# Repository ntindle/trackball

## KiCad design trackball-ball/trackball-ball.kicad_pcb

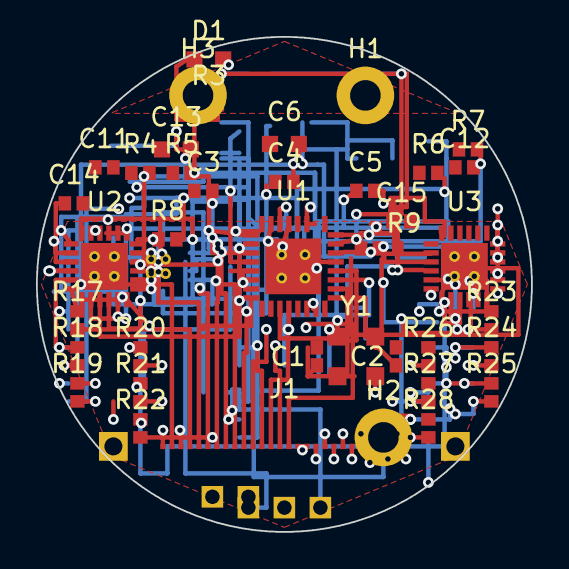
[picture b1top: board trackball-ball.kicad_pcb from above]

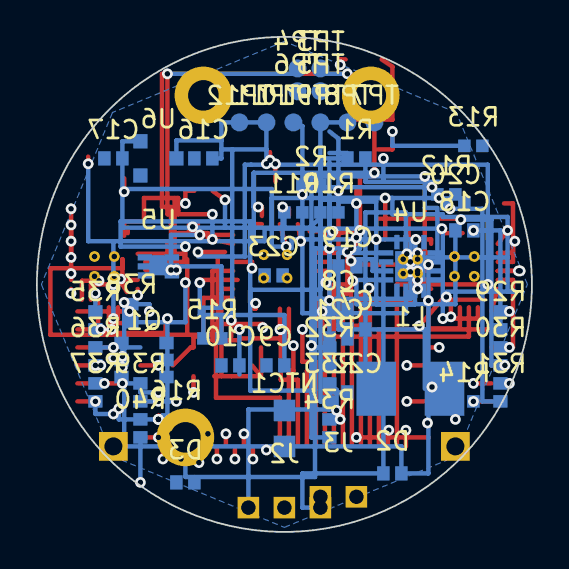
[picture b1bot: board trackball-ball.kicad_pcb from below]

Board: 4 copper layers, 27.5 x 27.5 mm, 92 parts (53 on the bottom side), 85 nets.

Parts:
C1, C2: 12pF-NP0; C_0402_1005Metric
C3, C4, C5, C11, C12: 100nF-X7R-0402; C_0402_1005Metric
C6, C13: 4.7uF-X7R-0603-10V; C_0603_1608Metric
C7, C8, C9, C10: 100nF-X7R-0402-10V; C_0402_1005Metric
C14, C15: 2.2nF-NP0-0402; C_0402_1005Metric
C16, C17: 1uF-X7R-0603-10V; C_0402_1005Metric
C18: 2.2uF-X7R-0603-10V; C_0402_1005Metric
C19, C23: 0.1uF-0603-10V; C_0402_1005Metric
C20: 10uF-X7R-0603-10V; C_0402_1005Metric
C21: 22uF-X5R-0603-10V; C_0402_1005Metric
C22: DHC-TBD-0603; C_0402_1005Metric
D1: GREEN-0603; LED-0603_1608Metric
D2, D3: TPD1E05U06; ESD-1005-2P
H1, H2, H3: M1.6-NPTH; MOUNT-HOLE-3.2
J1: FH28D-28S; FH28D-28S-0.5SH
J2: JST-PH-3; JST-PH-3_SMD-TH
J3: JST-PH-2; JST-PH-2_SMD-TH
L1: 47uH-SLF6028; IND-SLF6028-6x6
NTC1: 10k-NTC-flying; NTC-PADS-2P
Q1: DMG6968U; SOT-23-6_2.9x1.6mm
R1: 1M-1pct-0402; R_0402_1005Metric
R2: 330k-1pct-0402; R_0402_1005Metric
R3: 200R-0402; R_0402_1005Metric
R4, R5: 4.7k-0402; R_0402_1005Metric
R6, R7, R8, R9: 10k-0402; R_0402_1005Metric
R10, R11: 10k; R_0402_1005Metric
R12: 150k; R_0402_1005Metric
R13: 100k; R_0402_1005Metric
R14: 20k-1pct; R_0402_1005Metric
R15: 1M-1pct; R_0402_1005Metric
R16: 330k-1pct; R_0402_1005Metric
R17, R18, R19, R20, R21, R22, R23, R24, R25, R26, R27, R28, R29, R30, R31, R32, R33, R34, R35, R36, R37, R38, R39, R40: 560R-0402; R_0402_1005Metric
TP3: SWDIO; TP-PAD-D1.0
TP4: SWDCLK; TP-PAD-D1.0
TP5: +3V0; TP-PAD-D1.0
TP6: GND; TP-PAD-D1.0
TP7: NRESET_TP; TP-PAD-D1.0
TP8: TP_SPARE; TP-PAD-D1.0
TP9: CHRG; TP-PAD-D1.0
TP10: FAULT; TP-PAD-D1.0
TP11: VBAT; TP-PAD-D1.0
TP12: CELL_N; TP-PAD-D1.0
U1: NRF52810-QCAA; QFN-32-1EP_5x5mm_P0.5mm
U2: CY8CMBR3116-0x37; QFN-24-1EP_4x4mm_P0.5mm
U3: CY8CMBR3116-0x38; QFN-24-1EP_4x4mm_P0.5mm
U4: LTC4120-4.2; QFN-16-1EP_3x3mm_P0.5mm
U5: BQ29700; WSON-6-EP_2x2mm_P0.65mm
U6: XC6206P302; SOT-23_2.9x1.3mm
Y1: 32MHz-CL9pF; Crystal-3225-4P

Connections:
+3V0: C3.1, C4.1, C5.1, C6.1, C11.1, C12.1, C13.1, C17.1, R4.1, R5.1, R6.1, R7.1, R8.1, R9.1, R10.2, R11.2, TP5.1, U1.9, U1.25, U1.32, U2.7, U3.7, U6.2
ANT_FEED: J1.2, U1.19
CELL_N: C23.2, J3.2, Q1.6, TP12.1, U5.4, U5.7
CHRG: R10.1, TP9.1, U1.6, U4.14
DHC_SNS: C22.2, J2.3
DHC_U4: C22.1, U4.6
FAULT: R11.1, TP10.1, U1.5, U4.15
GND: C1.2, C2.2, C3.2, C4.2, C5.2, C6.2, C7.2, C8.2, C9.2, C10.2, C11.2, C12.2, C13.2, C14.2, C15.2, C16.2, C17.2, C18.1, C20.2, C21.2, D1.2, D2.2, D3.2, J1.1, J1.3, J1.16, J2.2, NTC1.2, Q1.4, R2.2, R13.2, R14.2, R16.2, TP6.1, U1.20, U1.29, U1.33, U2.6, U2.8, U2.9, U2.10, U2.11, U2.12, U2.25, U3.6, U3.8, U3.9, U3.10, U3.11, U3.12, U3.25, U4.5, U4.7, U4.17, U6.1, Y1.2, Y1.4
HI1: R6.2, U1.10, U2.23
HI2: R7.2, U1.11, U3.23
I2C_SCL: D3.1, R5.2, U1.8, U2.22, U3.22
I2C_SDA: D2.1, R4.2, U1.7, U2.21, U3.21
LED_A: D1.1, R3.2
LED_DOT: R3.1, U1.14
NTC_CELL: NTC1.1, U4.12
RUN_RX: R12.2, R13.1, U4.16
SW_RX: C19.2, L1.1, U4.4
T00: J1.4, R17.2
T01: J1.5, R18.2
T02: J1.6, R19.2
T03: J1.7, R20.2
T04: J1.8, R21.2
T05: J1.9, R22.2
T06: J1.10, R23.2
T07: J1.11, R24.2
T08: J1.12, R25.2
T09: J1.13, R26.2
T10: J1.14, R27.2
T11: J1.15, R28.2
T12: J1.17, R29.2
T13: J1.18, R30.2
T14: J1.19, R31.2
T15: J1.20, R32.2
T16: J1.21, R33.2
T17: J1.22, R34.2
T18: J1.23, R35.2
T19: J1.24, R36.2
T20: J1.25, R37.2
T21: J1.26, R38.2
T22: J1.27, R39.2
T23: J1.28, R40.2
U1_DEC3: C9.1, U1.22
U1_DEC4: C10.1, U1.30
U2_CMOD: C14.1, U2.5
U2_CS0: R17.1, U2.1
U2_CS1: R18.1, U2.2
U2_CS2: R19.1, U2.3
U2_CS3: R20.1, U2.4
U2_CS4: R21.1, U2.20
U2_CS5: R22.1, U2.19
U2_CS6: R23.1, U2.18
U2_CS7: R24.1, U2.17
U2_CS8: R25.1, U2.16
U2_CS9: R26.1, U2.15
U2_CS10: R27.1, U2.14
U2_CS11: R28.1, U2.13
U3_CMOD: C15.1, U3.5
U3_CS0: R29.1, U3.1
U3_CS1: R30.1, U3.2
U3_CS2: R31.1, U3.3
U3_CS3: R32.1, U3.4
U3_CS4: R33.1, U3.20
U3_CS5: R34.1, U3.19
U3_CS6: R35.1, U3.18
U3_CS7: R36.1, U3.17
U3_CS8: R37.1, U3.16
U3_CS9: R38.1, U3.15
U3_CS10: R39.1, U3.14
U3_CS11: R40.1, U3.13
U4_BOOST: C19.1, U4.2
U4_CHGSNS: L1.2, U4.8
U4_INTVCC: C18.2, U4.1
U4_PROG: R14.1, U4.13
U5_BAT: C23.1, R15.2, U5.5
U5_COUT: Q1.5, U5.2
U5_DOUT: Q1.2, U5.3
U5_MID: Q1.1, Q1.3
U5_VM: R16.1, U5.6
VBAT: C16.1, C21.1, J3.1, R1.1, R15.1, TP11.1, U4.9, U4.10, U6.3
VBAT_SNS: R1.2, R2.1, U1.4
VIN_RX: C20.1, J2.1, R12.1, U4.3
XC_A: C1.1, U1.23, Y1.1
XC_B: C2.1, U1.24, Y1.3
XRES1: R8.2, U1.12, U2.24
XRES2: R9.2, U1.13, U3.24

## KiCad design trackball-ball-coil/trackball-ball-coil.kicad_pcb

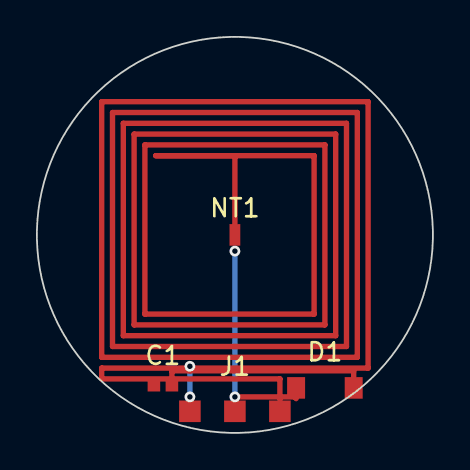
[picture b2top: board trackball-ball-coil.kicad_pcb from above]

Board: 2 copper layers, 22.0 x 22.0 mm, 4 parts (0 on the bottom side), 3 nets.

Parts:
C1: 100nF-TBD; C_0402
D1: 12V-TBD; D_SOD123
J1: WIRE-3; WIREPADS-3
NT1: NET-TIE; NET-TIE-2

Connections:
GND: D1.1, J1.2, NT1.2
RX_A: C1.1, J1.3, NT1.1
VIN_RX: C1.2, D1.2, J1.1

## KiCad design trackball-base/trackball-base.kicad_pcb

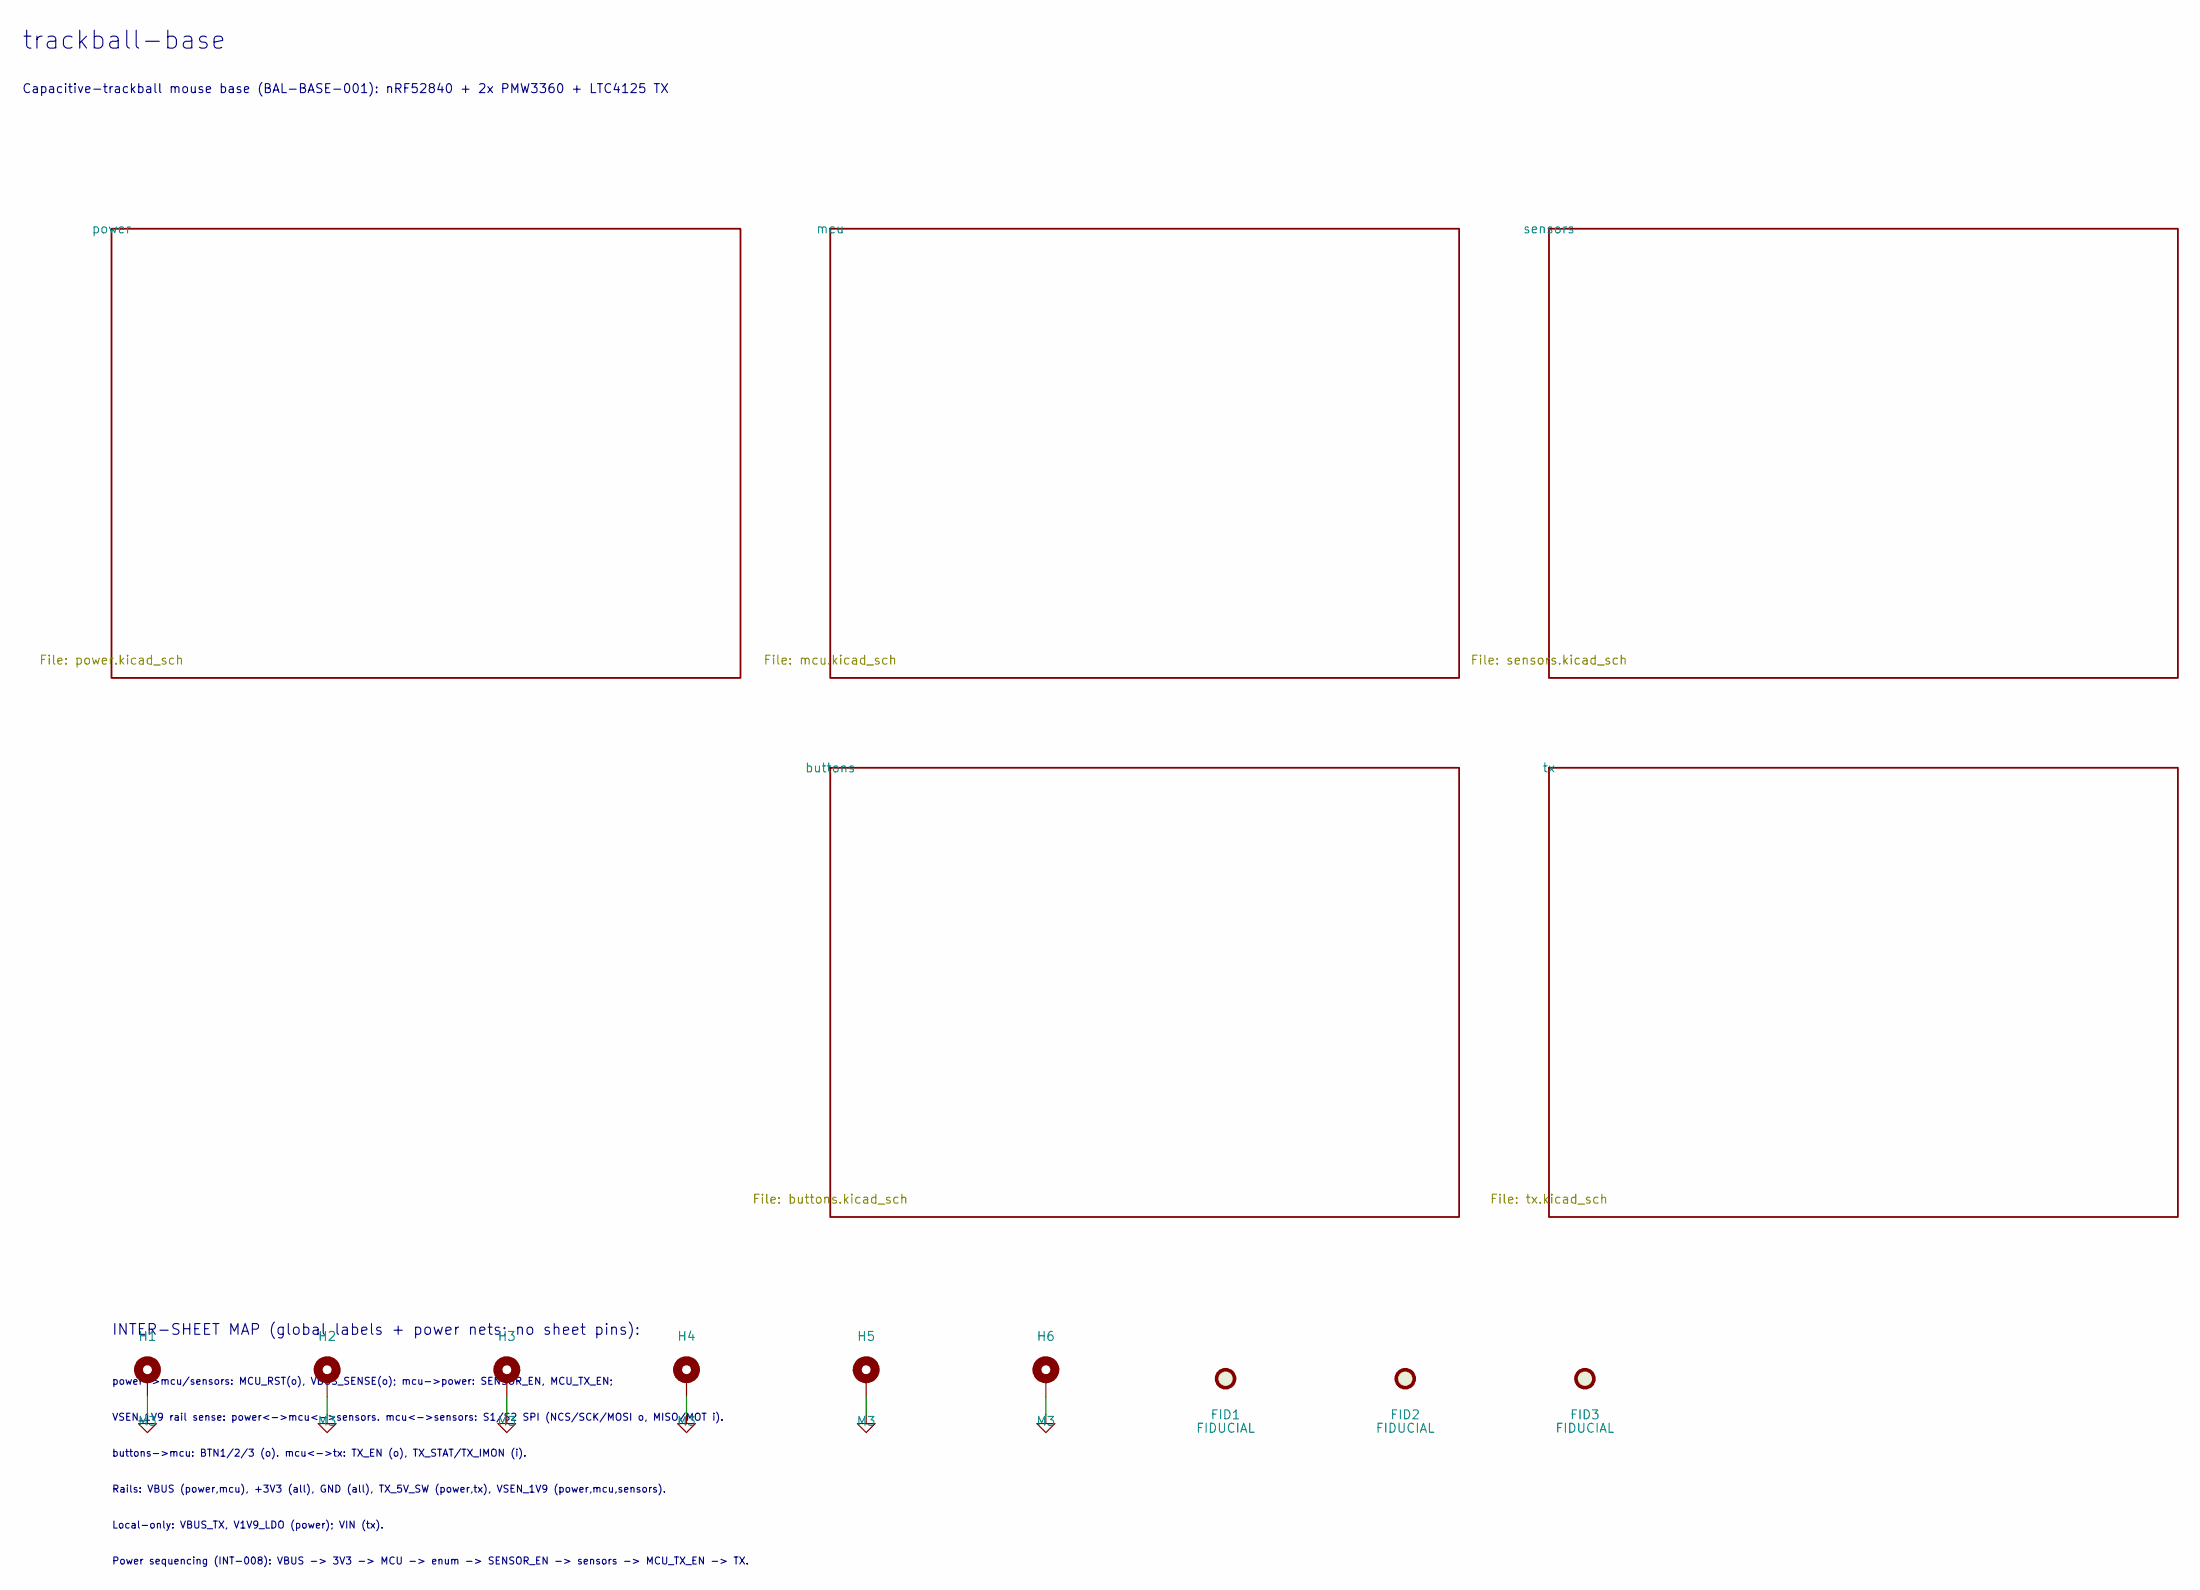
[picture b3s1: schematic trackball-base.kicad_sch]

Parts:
FID1, FID2, FID3: FIDUCIAL; Fiducial_1mm_Mask2mm
H1, H2, H3, H4, H5, H6: M3; MountingHole_3.2mm_M3_Pad

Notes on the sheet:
trackball-base
Capacitive-trackball mouse base (BAL-BASE-001): nRF52840 + 2x PMW3360 + LTC4125 TX
INTER-SHEET MAP (global labels + power nets; no sheet pins):
power->mcu/sensors: MCU_RST(o), VBUS_SENSE(o); mcu->power: SENSOR_EN, MCU_TX_EN;
VSEN_1V9 rail sense: power<->mcu<->sensors. mcu<->sensors: S1/S2 SPI (NCS/SCK/MOSI o, MISO/MOT i).
buttons->mcu: BTN1/2/3 (o). mcu<->tx: TX_EN (o), TX_STAT/TX_IMON (i).
Rails: VBUS (power,mcu), +3V3 (all), GND (all), TX_5V_SW (power,tx), VSEN_1V9 (power,mcu,sensors).
Local-only: VBUS_TX, V1V9_LDO (power); VIN (tx).
Power sequencing (INT-008): VBUS -> 3V3 -> MCU -> enum -> SENSOR_EN -> sensors -> MCU_TX_EN -> TX.

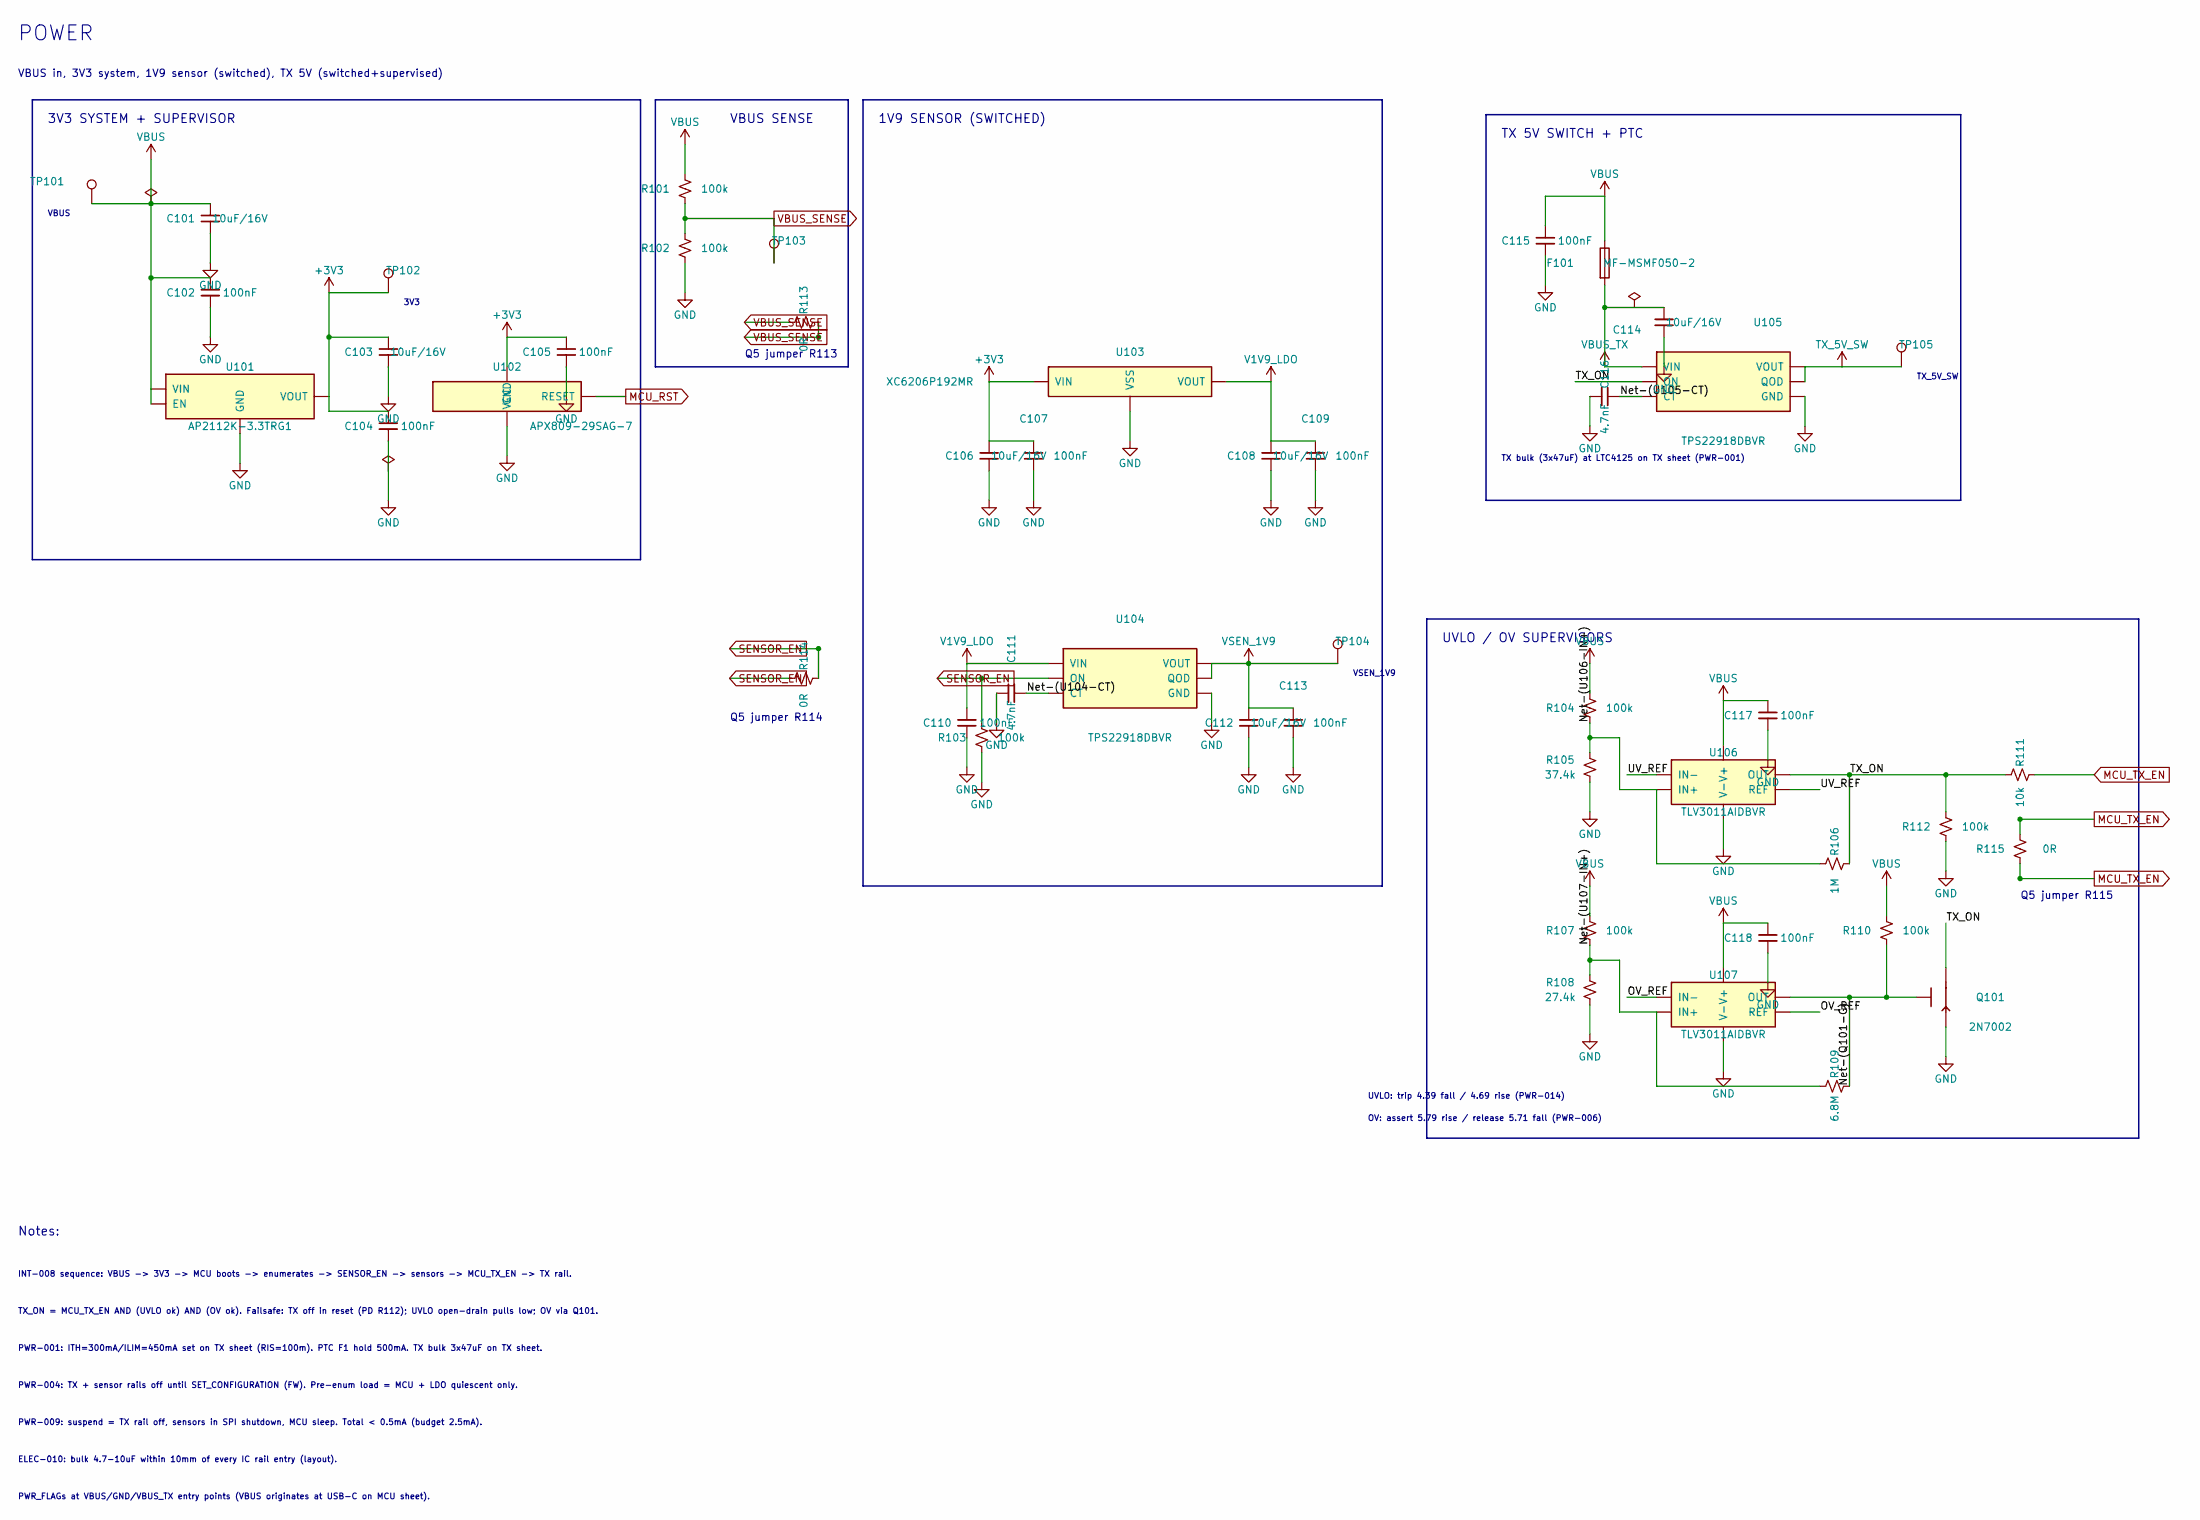
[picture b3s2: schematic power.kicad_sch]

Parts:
C101, C103, C106, C108, C112, C114: 10uF/16V; C_0805_2012Metric
C102, C104, C105, C107, C109, C110, C113, C115, C117, C118: 100nF; C_0603_1608Metric
C111, C116: 4.7nF; C_0603_1608Metric
F101: MF-MSMF050-2; Fuse_1812_4532Metric
Q101: 2N7002; SOT-23
R101, R102, R103, R104, R107, R110, R112: 100k; R_0603_1608Metric
R105: 37.4k; R_0603_1608Metric
R106: 1M; R_0603_1608Metric
R108: 27.4k; R_0603_1608Metric
R109: 6.8M; R_0603_1608Metric
R111: 10k; R_0603_1608Metric
R113, R114, R115: 0R; R_0603_1608Metric
TP101: TP101; TestPoint_Pad_D1.5mm
TP102: TP102; TestPoint_Pad_D1.5mm
TP103: TP103; TestPoint_Pad_D1.5mm
TP104: TP104; TestPoint_Pad_D1.5mm
TP105: TP105; TestPoint_Pad_D1.5mm
U101: AP2112K-3.3TRG1; SOT-23-5
U102: APX809-29SAG-7; SOT-23
U103: XC6206P192MR; SOT-23
U104, U105: TPS22918DBVR; SOT-23-6
U106, U107: TLV3011AIDBVR; SOT-23-6

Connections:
+3V3: C103.1, C104.1, C105.1, C106.1, C107.1, TP102.1, U101.5 (VOUT), U102.3 (VCC), U103.3 (VIN); also elsewhere on the board
/power/Net-(Q101-G): Q101.1 (G), R109.2, R110.2, U107.1 (OUT)
/power/Net-(U104-CT): C111.2, U104.4 (CT)
/power/Net-(U105-CT): C116.2, U105.4 (CT)
/power/Net-(U106-IN+): R104.2, R105.1, R106.1, U106.3 (IN+)
/power/Net-(U107-IN+): R107.2, R108.1, R109.1, U107.3 (IN+)
/power/OV_REF: U107.4 (IN-), U107.5 (REF)
/power/TX_ON: Q101.3 (D), R106.2, R111.1, R112.1, U105.3 (ON), U106.1 (OUT)
/power/UV_REF: U106.4 (IN-), U106.5 (REF)
MCU_RST: U102.2 (RESET); also elsewhere on the board
MCU_TX_EN: R111.2, R115.1, R115.2; also elsewhere on the board
SENSOR_EN: R103.1, R114.1, R114.2, U104.3 (ON); also elsewhere on the board
TX_5V_SW: TP105.1, U105.5 (QOD), U105.6 (VOUT); also elsewhere on the board
V1V9_LDO: C108.1, C109.1, C110.1, U103.2 (VOUT), U104.1 (VIN)
VBUS_SENSE: R101.2, R102.1, R113.1, R113.2, TP103.1; also elsewhere on the board
VSEN_1V9: C112.1, C113.1, TP104.1, U104.5 (QOD), U104.6 (VOUT); also elsewhere on the board

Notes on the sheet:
POWER
VBUS in, 3V3 system, 1V9 sensor (switched), TX 5V (switched+supervised)
3V3 SYSTEM + SUPERVISOR
VBUS
3V3
VBUS SENSE
1V9 SENSOR (SWITCHED)
VSEN_1V9
TX 5V SWITCH + PTC
TX_5V_SW
TX bulk (3x47uF) at LTC4125 on TX sheet (PWR-001)
UVLO / OV SUPERVISORS
UVLO: trip 4.39 fall / 4.69 rise (PWR-014)
OV: assert 5.79 rise / release 5.71 fall (PWR-006)
Notes:
INT-008 sequence: VBUS -> 3V3 -> MCU boots -> enumerates -> SENSOR_EN -> sensors -> MCU_TX_EN -> TX rail.
TX_ON = MCU_TX_EN AND (UVLO ok) AND (OV ok). Failsafe: TX off in reset (PD R112); UVLO open-drain pulls low; OV via Q101.
PWR-001: ITH=300mA/ILIM=450mA set on TX sheet (RIS=100m). PTC F1 hold 500mA. TX bulk 3x47uF on TX sheet.
PWR-004: TX + sensor rails off until SET_CONFIGURATION (FW). Pre-enum load = MCU + LDO quiescent only.
PWR-009: suspend = TX rail off, sensors in SPI shutdown, MCU sleep. Total < 0.5mA (budget 2.5mA).
ELEC-010: bulk 4.7-10uF within 10mm of every IC rail entry (layout).
PWR_FLAGs at VBUS/GND/VBUS_TX entry points (VBUS originates at USB-C on MCU sheet).
Q5 jumper R113
Q5 jumper R114
Q5 jumper R115

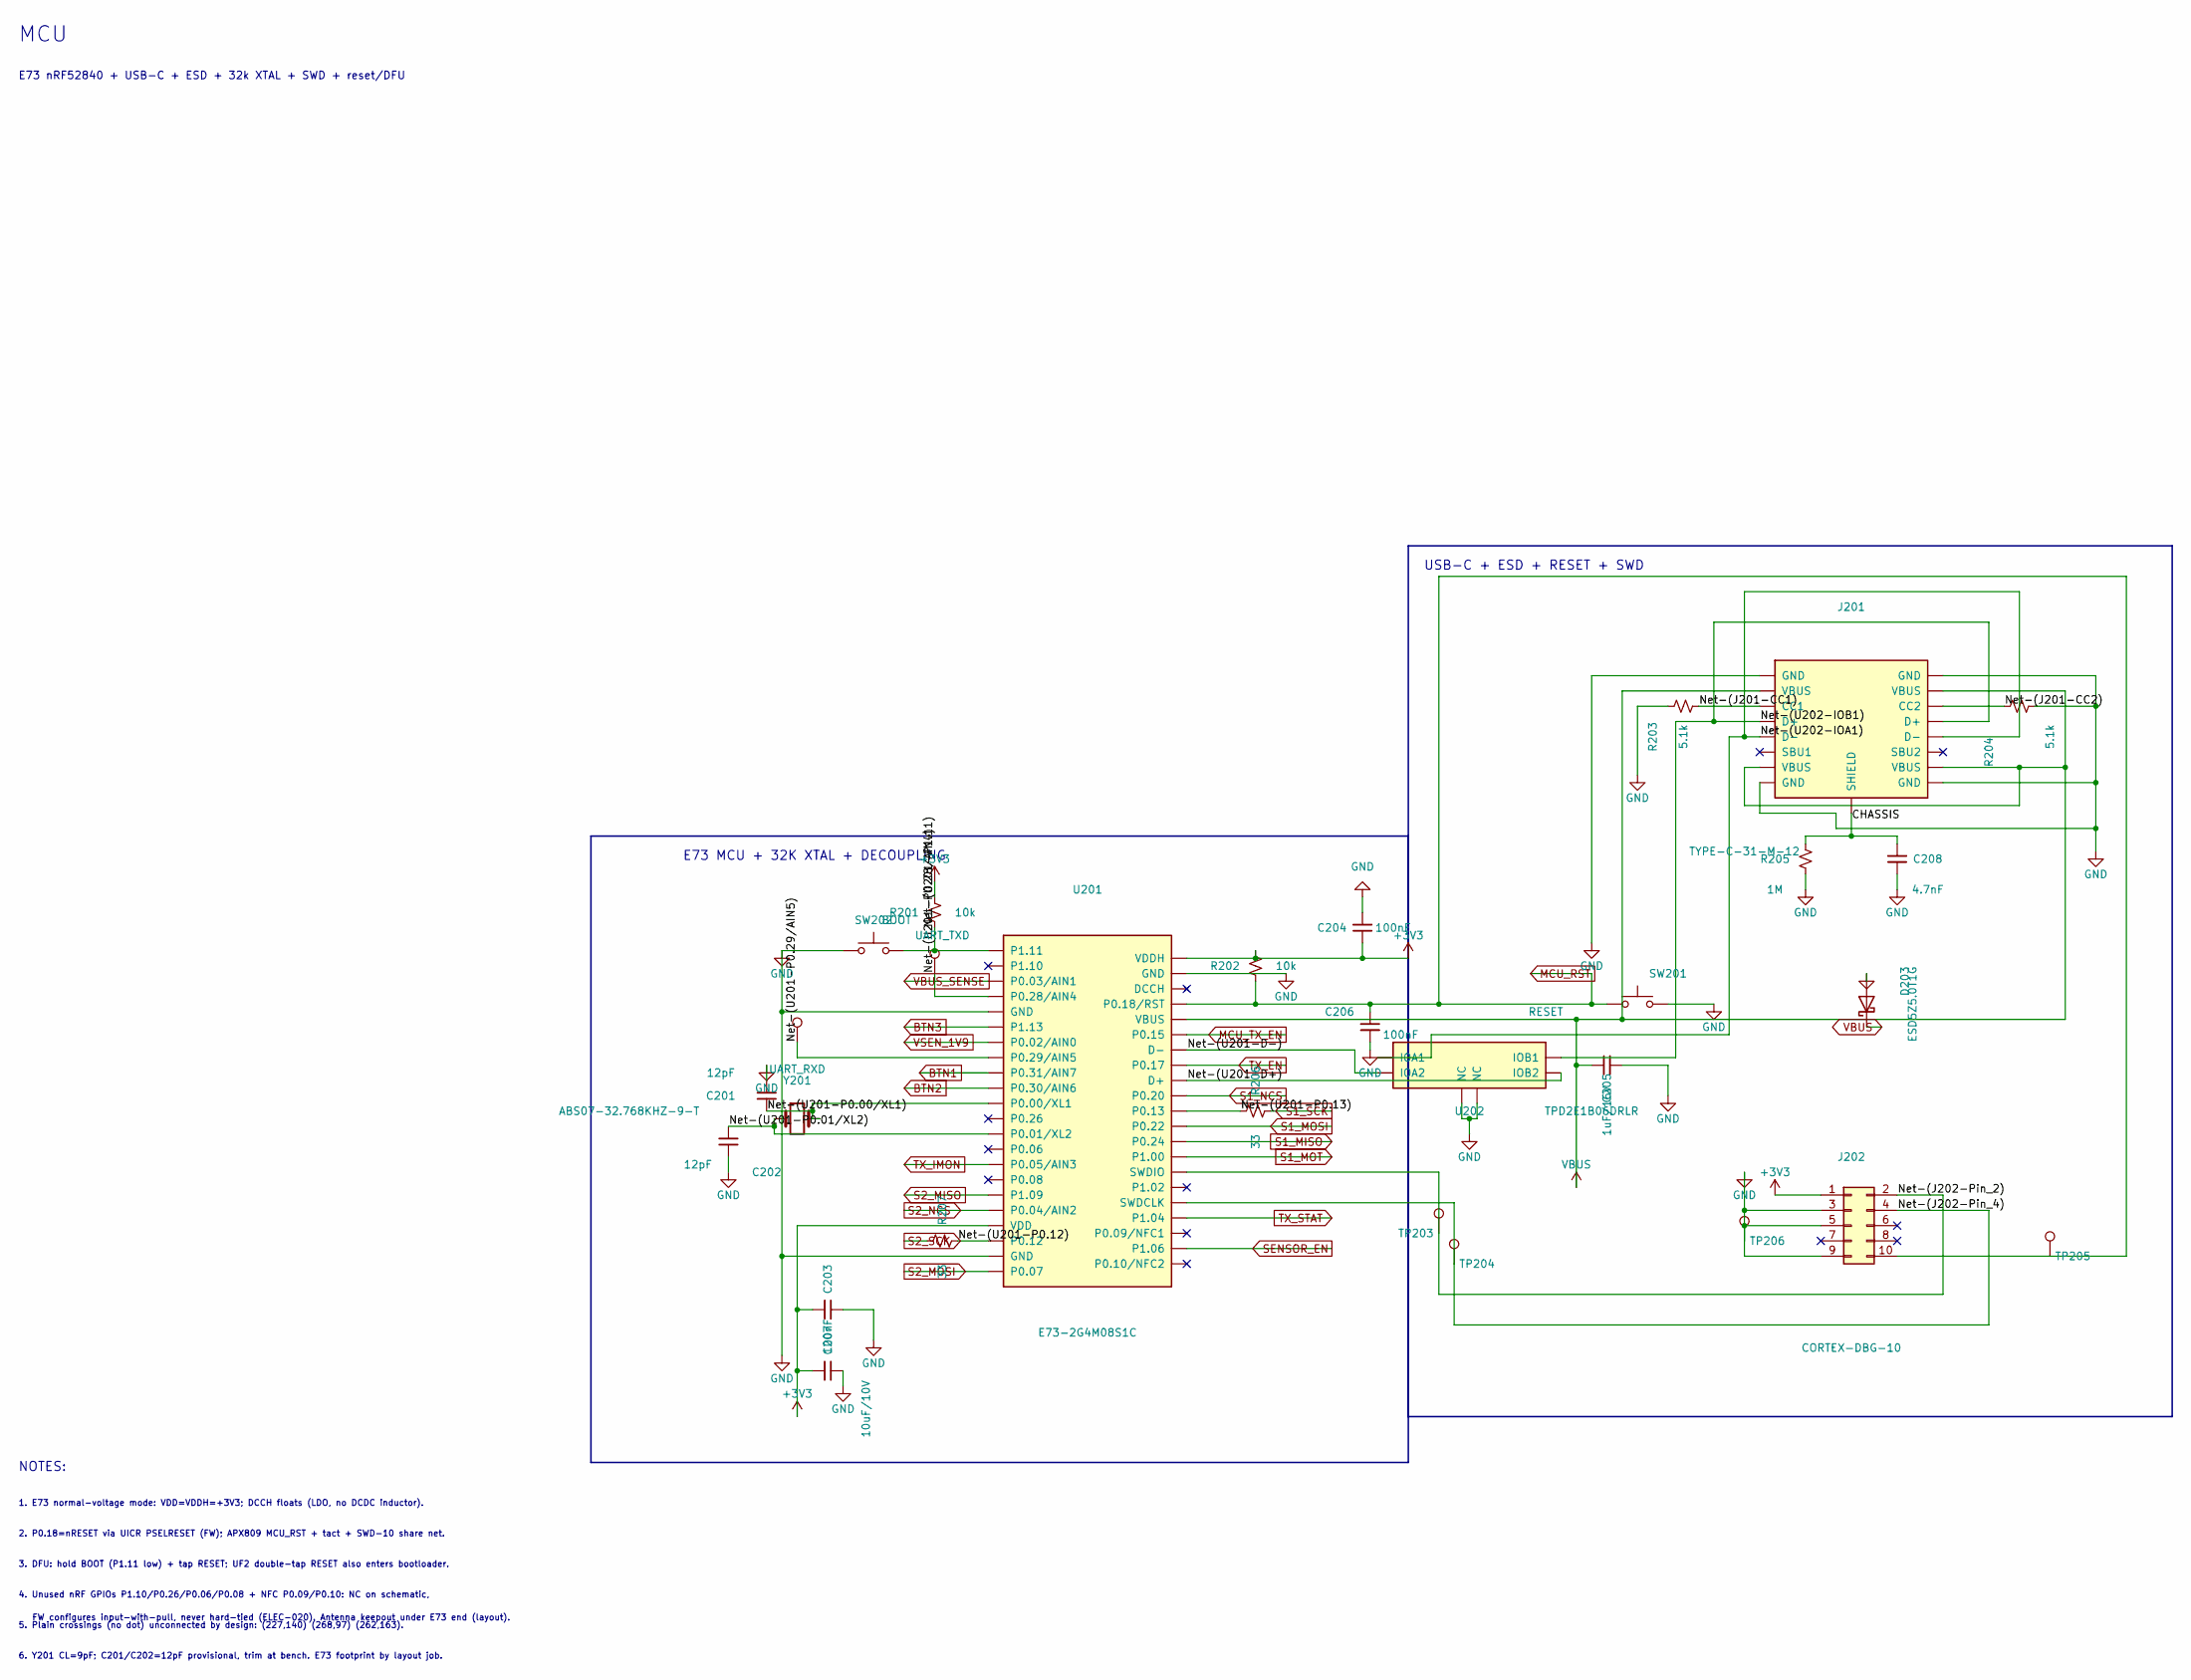
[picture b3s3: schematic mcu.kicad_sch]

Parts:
C201, C202: 12pF; C_0603_1608Metric
C203, C204: 100nF; C_0402_1005Metric
C205: 1uF/16V; C_0603_1608Metric
C206: 100nF; C_0603_1608Metric
C207: 10uF/10V; C_0805_2012Metric
C208: 4.7nF; C_0603_1608Metric
D203: ESD5Z5.0T1G; D_SOD-523
J201: TYPE-C-31-M-12; USB_C_Receptacle_HRO_TYPE-C-31-M-12
J202: CORTEX-DBG-10; PinHeader_2x05_P1.27mm_Vertical_SMD
R201, R202: 10k; R_0603_1608Metric
R203, R204: 5.1k; R_0603_1608Metric
R205: 1M; R_0603_1608Metric
R206, R207: 33; R_0603_1608Metric
SW201: RESET; SW_SPST_B3S-1000
SW202: BOOT; SW_SPST_B3S-1000
TP201: UART_TXD; TestPoint_Pad_D1.5mm
TP202: UART_RXD; TestPoint_Pad_D1.5mm
TP203: TP203; TestPoint_Pad_D2.0mm
TP204: TP204; TestPoint_Pad_D2.0mm
TP205: TP205; TestPoint_Pad_D2.0mm
TP206: TP206; TestPoint_Pad_D2.0mm
U201: E73-2G4M08S1C
U202: TPD2E1B06DRLR; SOT-563
Y201: ABS07-32.768KHZ-9-T; Crystal_SMD_3215-2Pin_3.2x1.5mm

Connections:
+3V3: C203.1, C204.2, C207.1, J202.1, R201.1, R202.1, U201.19 (VDD), U201.23 (VDDH); also elsewhere on the board
/mcu/CHASSIS: C208.1, J201.SH (SHIELD), R205.1
/mcu/Net-(J201-CC1): J201.A5 (CC1), R203.2
/mcu/Net-(J201-CC2): J201.B5 (CC2), R204.1
/mcu/Net-(J202-Pin_2): J202.2, TP203.1, U201.37 (SWDIO)
/mcu/Net-(J202-Pin_4): J202.4, TP204.1, U201.39 (SWDCLK)
/mcu/Net-(U201-D+): U201.31 (D+), U202.4 (IOB2)
/mcu/Net-(U201-D-): U201.29 (D-), U202.5 (IOA2)
/mcu/Net-(U201-P0.00/XL1): C201.2, U201.11 (P0.00/XL1), Y201.2
/mcu/Net-(U201-P0.01/XL2): C202.1, U201.13 (P0.01/XL2), Y201.1
/mcu/Net-(U201-P0.12): R207.2, U201.20 (P0.12)
/mcu/Net-(U201-P0.13): R206.1, U201.33 (P0.13)
/mcu/Net-(U201-P0.28/AIN4): TP201.1, U201.4 (P0.28/AIN4)
/mcu/Net-(U201-P0.29/AIN5): TP202.1, U201.8 (P0.29/AIN5)
/mcu/Net-(U201-P1.11): R201.2, SW202.2, U201.1 (P1.11)
/mcu/Net-(U202-IOA1): J201.A7 (D-), J201.B7 (D-), U202.1 (IOA1)
/mcu/Net-(U202-IOB1): J201.A6 (D+), J201.B6 (D+), U202.2 (IOB1)
BTN1: U201.9 (P0.31/AIN7); also elsewhere on the board
BTN2: U201.10 (P0.30/AIN6); also elsewhere on the board
BTN3: U201.6 (P1.13); also elsewhere on the board
MCU_RST: C206.1, J202.10, R202.2, SW201.1, TP205.1, U201.26 (P0.18/RST); also elsewhere on the board
MCU_TX_EN: U201.28 (P0.15); also elsewhere on the board
S1_MISO: U201.35 (P0.24); also elsewhere on the board
S1_MOSI: U201.34 (P0.22); also elsewhere on the board
S1_MOT: U201.36 (P1.00); also elsewhere on the board
S1_NCS: U201.32 (P0.20); also elsewhere on the board
S1_SCK: R206.2; also elsewhere on the board
S2_MISO: U201.17 (P1.09); also elsewhere on the board
S2_MOSI: U201.22 (P0.07); also elsewhere on the board
S2_NCS: U201.18 (P0.04/AIN2); also elsewhere on the board
S2_SCK: R207.1; also elsewhere on the board
SENSOR_EN: U201.42 (P1.06); also elsewhere on the board
TX_EN: U201.30 (P0.17); also elsewhere on the board
TX_IMON: U201.15 (P0.05/AIN3); also elsewhere on the board
TX_STAT: U201.40 (P1.04); also elsewhere on the board
VBUS_SENSE: U201.3 (P0.03/AIN1); also elsewhere on the board
VSEN_1V9: U201.7 (P0.02/AIN0); also elsewhere on the board

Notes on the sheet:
MCU
E73 nRF52840 + USB-C + ESD + 32k XTAL + SWD + reset/DFU
E73 MCU + 32K XTAL + DECOUPLING
USB-C + ESD + RESET + SWD
NOTES:
1. E73 normal-voltage mode: VDD=VDDH=+3V3; DCCH floats (LDO, no DCDC inductor).
2. P0.18=nRESET via UICR PSELRESET (FW); APX809 MCU_RST + tact + SWD-10 share net.
3. DFU: hold BOOT (P1.11 low) + tap RESET; UF2 double-tap RESET also enters bootloader.
4. Unused nRF GPIOs P1.10/P0.26/P0.06/P0.08 + NFC P0.09/P0.10: NC on schematic,
FW configures input-with-pull, never hard-tied (ELEC-020). Antenna keepout under E73 end (layout).
5. Plain crossings (no dot) unconnected by design: (227,140) (268,97) (262,163).
6. Y201 CL=9pF; C201/C202=12pF provisional, trim at bench. E73 footprint by layout job.

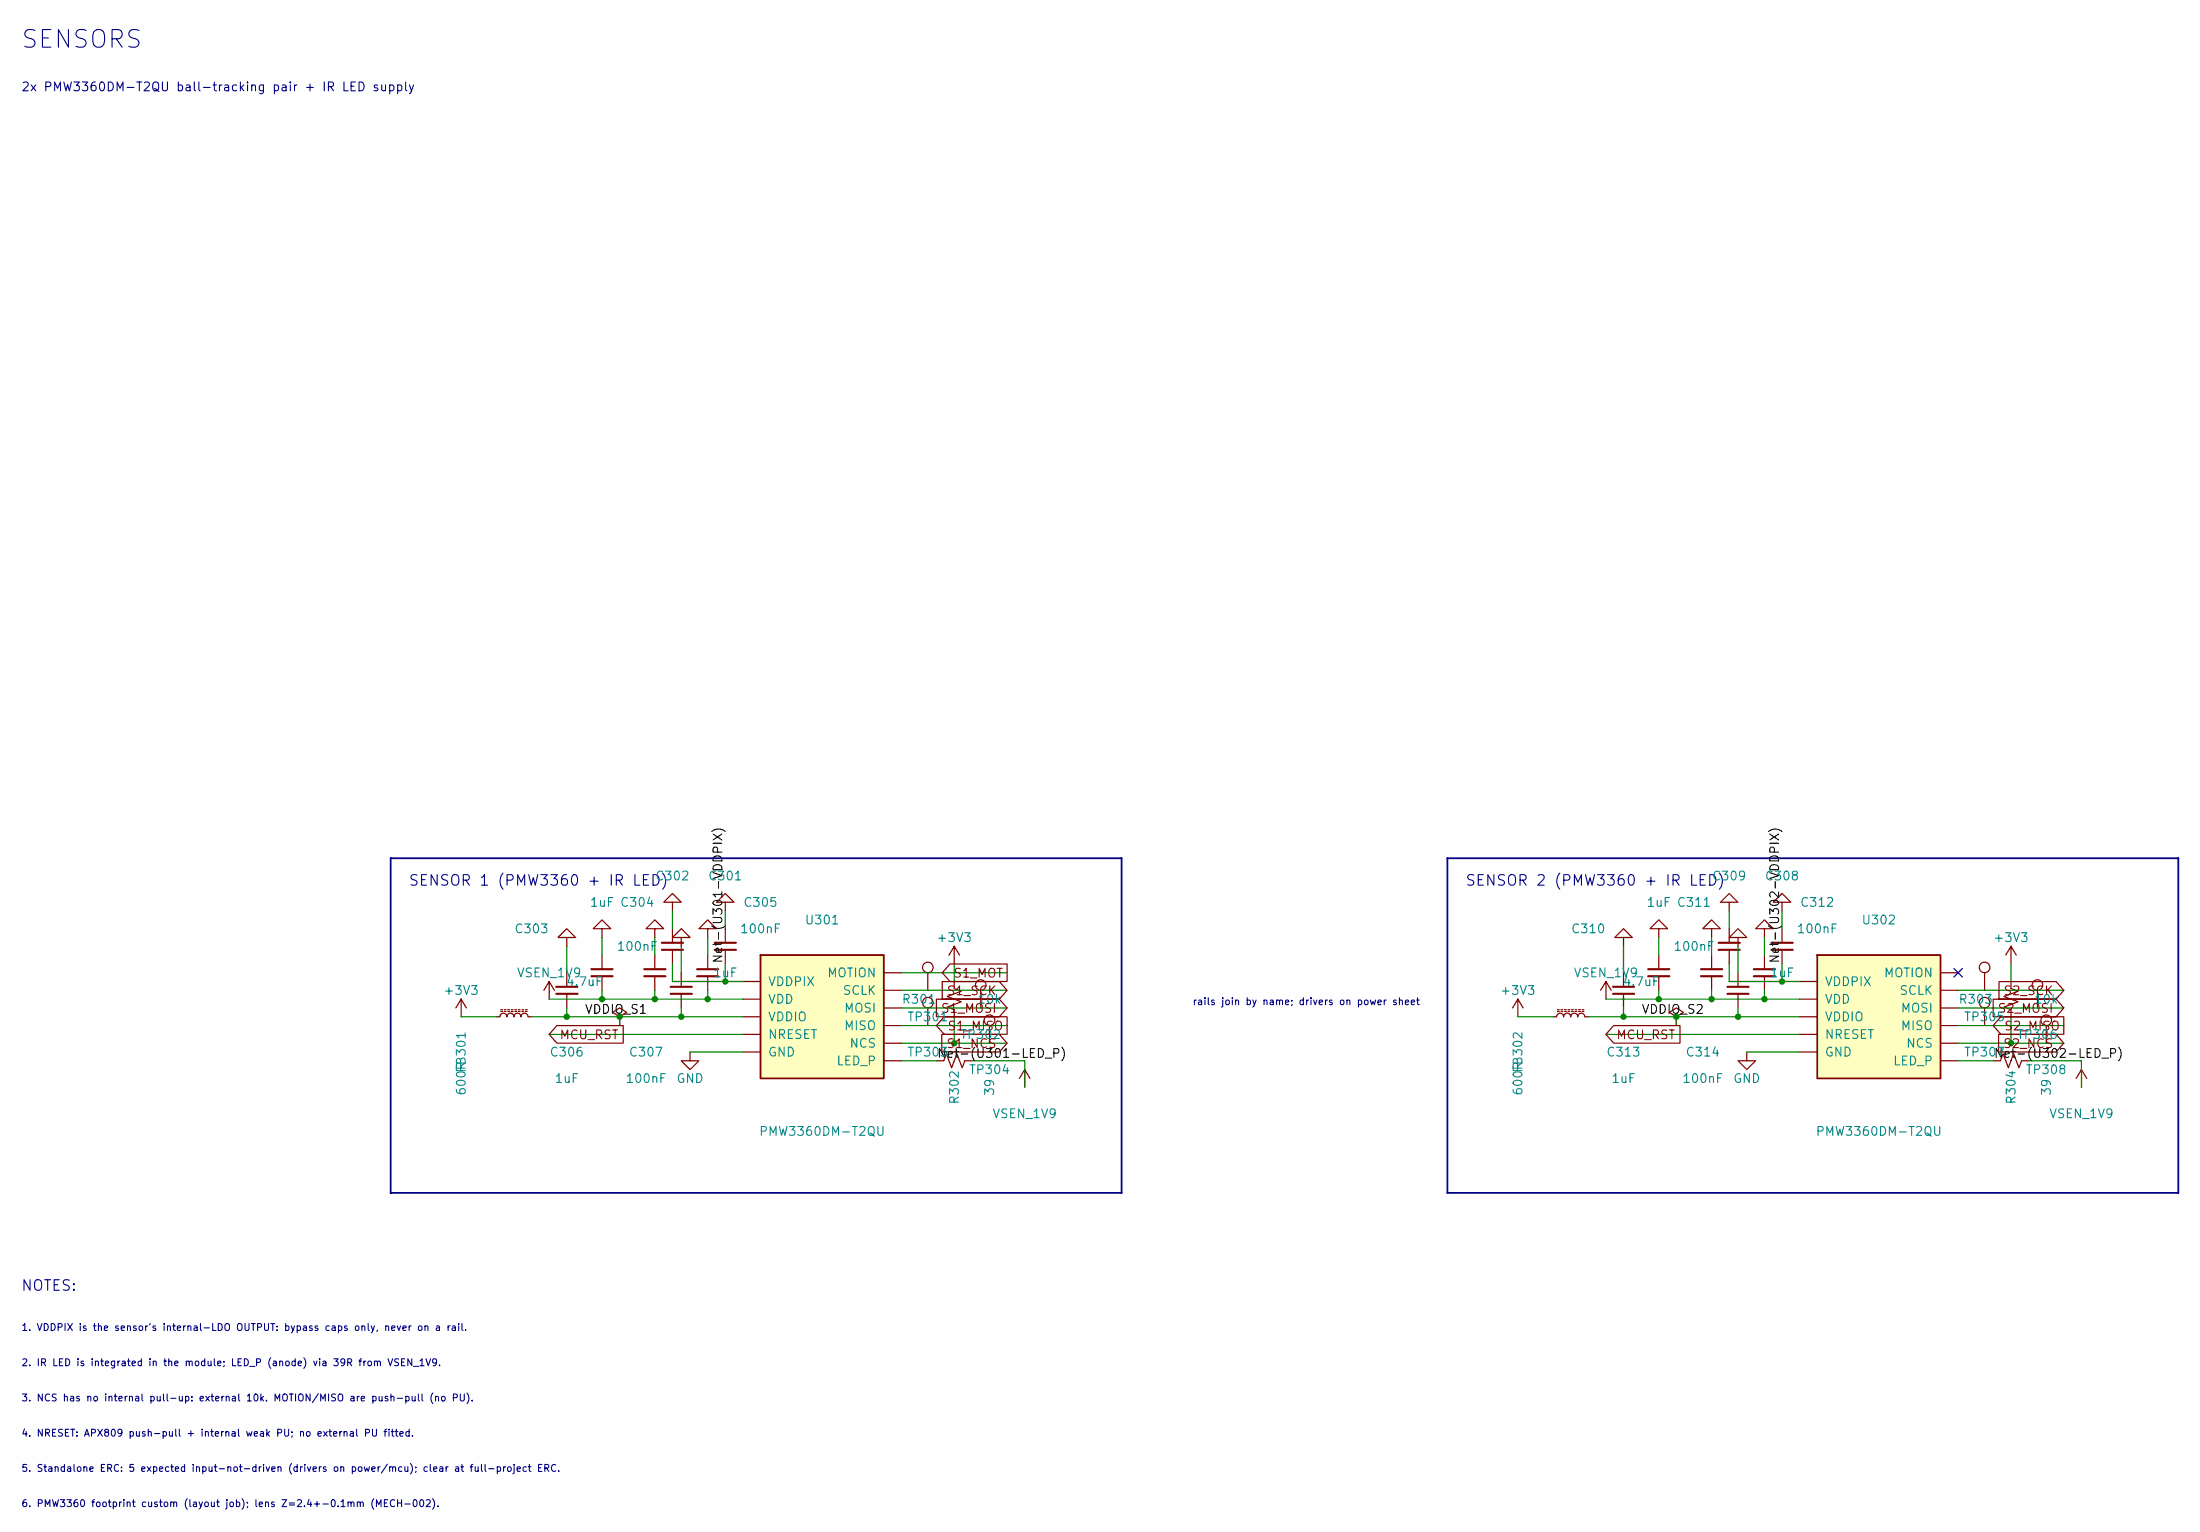
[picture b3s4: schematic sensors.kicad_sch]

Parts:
C301, C304, C306, C308, C311, C313: 1uF; C_0603_1608Metric
C302, C305, C307, C309, C312, C314: 100nF; C_0603_1608Metric
C303, C310: 4.7uF; C_0603_1608Metric
FB301, FB302: 600R; L_0603_1608Metric
R301, R303: 10k; R_0603_1608Metric
R302, R304: 39; R_0603_1608Metric
TP301: TP301; TestPoint_Pad_D1.5mm
TP302: TP302; TestPoint_Pad_D1.5mm
TP303: TP303; TestPoint_Pad_D1.5mm
TP304: TP304; TestPoint_Pad_D1.5mm
TP305: TP305; TestPoint_Pad_D1.5mm
TP306: TP306; TestPoint_Pad_D1.5mm
TP307: TP307; TestPoint_Pad_D1.5mm
TP308: TP308; TestPoint_Pad_D1.5mm
U301, U302: PMW3360DM-T2QU

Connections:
+3V3: FB301.1, FB302.1, R301.1, R303.1; also elsewhere on the board
/sensors/Net-(U301-LED_P): R302.1, U301.15 (LED_P)
/sensors/Net-(U301-VDDPIX): C301.2, C302.2, U301.3 (VDDPIX)
/sensors/Net-(U302-LED_P): R304.1, U302.15 (LED_P)
/sensors/Net-(U302-VDDPIX): C308.2, C309.2, U302.3 (VDDPIX)
MCU_RST: U301.7 (NRESET), U302.7 (NRESET); also elsewhere on the board
S1_MISO: TP303.1, U301.12 (MISO); also elsewhere on the board
S1_MOSI: TP302.1, U301.11 (MOSI); also elsewhere on the board
S1_MOT: U301.9 (MOTION); also elsewhere on the board
S1_NCS: R301.2, TP304.1, U301.13 (NCS); also elsewhere on the board
S1_SCK: TP301.1, U301.10 (SCLK); also elsewhere on the board
S2_MISO: TP307.1, U302.12 (MISO); also elsewhere on the board
S2_MOSI: TP306.1, U302.11 (MOSI); also elsewhere on the board
S2_NCS: R303.2, TP308.1, U302.13 (NCS); also elsewhere on the board
S2_SCK: TP305.1, U302.10 (SCLK); also elsewhere on the board
VSEN_1V9: C303.2, C304.2, C305.2, C310.2, C311.2, C312.2, R302.2, R304.2, U301.4 (VDD), U302.4 (VDD); also elsewhere on the board

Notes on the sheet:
SENSORS
2x PMW3360DM-T2QU ball-tracking pair + IR LED supply
SENSOR 1 (PMW3360 + IR LED)
SENSOR 2 (PMW3360 + IR LED)
rails join by name; drivers on power sheet
NOTES:
1. VDDPIX is the sensor's internal-LDO OUTPUT: bypass caps only, never on a rail.
2. IR LED is integrated in the module; LED_P (anode) via 39R from VSEN_1V9.
3. NCS has no internal pull-up: external 10k. MOTION/MISO are push-pull (no PU).
4. NRESET: APX809 push-pull + internal weak PU; no external PU fitted.
5. Standalone ERC: 5 expected input-not-driven (drivers on power/mcu); clear at full-project ERC.
6. PMW3360 footprint custom (layout job); lens Z=2.4+-0.1mm (MECH-002).
